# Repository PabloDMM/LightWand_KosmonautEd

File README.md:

# LightWand_KosmonautEd
This repository contains all the files related to the LightWand Kosmonaut Edition, based on the original LightWand by Michael Ross ( http://mrossphoto.com/wordpress32/ )

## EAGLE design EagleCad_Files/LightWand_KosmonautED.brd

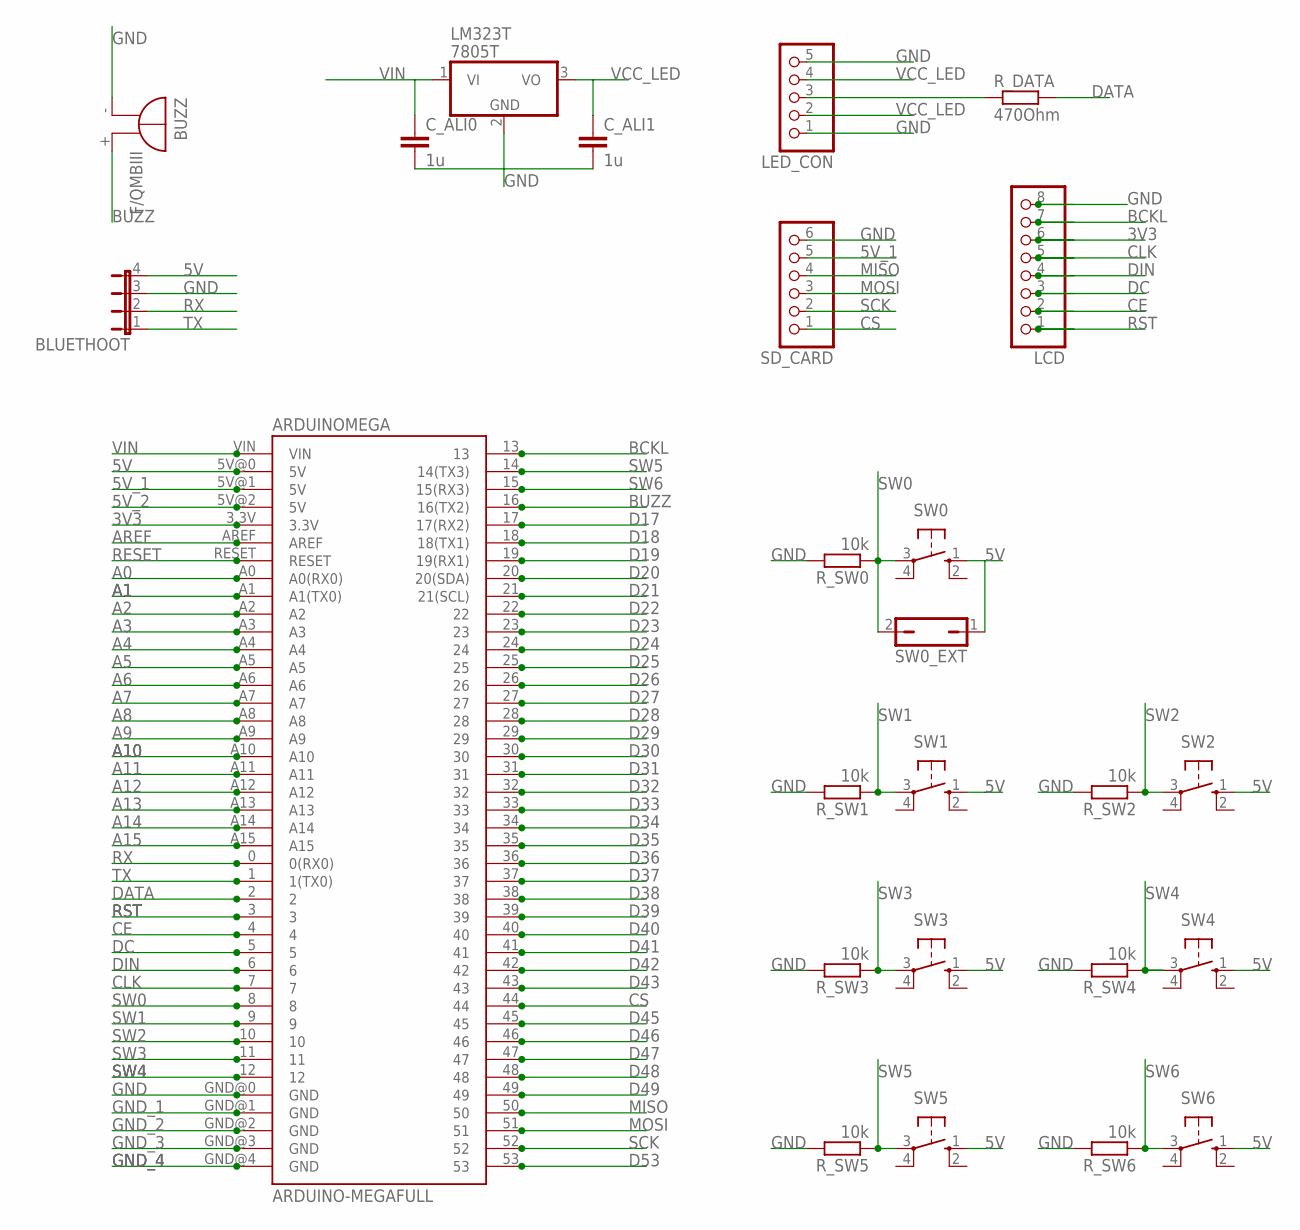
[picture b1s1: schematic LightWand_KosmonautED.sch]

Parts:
ARDUINOMEGA: ARDUINO-MEGAFULL; ARDUINO_MEGA
BLUETHOOT: JP4E; JP4
BUZZ: F/QMBIII
C_ALI0, C_ALI1: 1u; C1206
LCD: PINHD-1X8; 1X08
LED_CON: PINHD-1X5; 1X05
LM323T: 7805T; TO220H
R_DATA: 470Ohm; R1206
R_SW0, R_SW1, R_SW2, R_SW3, R_SW4, R_SW5, R_SW6: 10k; R1206
SD_CARD: PINHD-1X6; 1X06
SW0, SW1, SW2, SW3, SW4, SW5, SW6: 10-XX; B3F-10XX
SW0_EXT: JP1Q; JP1

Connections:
3V3: ARDUINOMEGA.3.3V, LCD.6
5V: ARDUINOMEGA.5V@0 (5V), BLUETHOOT.4, SW0.1 (S), SW0_EXT.1, SW1.1 (S), SW2.1 (S), SW3.1 (S), SW4.1 (S), SW5.1 (S), SW6.1 (S)
5V_1: ARDUINOMEGA.5V@1 (5V), SD_CARD.5
5V_2: ARDUINOMEGA.5V@2 (5V)
A0: ARDUINOMEGA.A0 (A0(RX0))
A1: ARDUINOMEGA.A1 (A1(TX0))
A2: ARDUINOMEGA.A2
A3: ARDUINOMEGA.A3
A4: ARDUINOMEGA.A4
A5: ARDUINOMEGA.A5
A6: ARDUINOMEGA.A6
A7: ARDUINOMEGA.A7
A8: ARDUINOMEGA.A8
A9: ARDUINOMEGA.A9
A10: ARDUINOMEGA.A10
A11: ARDUINOMEGA.A11
A12: ARDUINOMEGA.A12
A13: ARDUINOMEGA.A13
A14: ARDUINOMEGA.A14
A15: ARDUINOMEGA.A15
AREF: ARDUINOMEGA.AREF
BCKL: ARDUINOMEGA.13, LCD.7
BUZZ: ARDUINOMEGA.16 (16(TX2)), BUZZ.+ (-)
CE: ARDUINOMEGA.4, LCD.2
CLK: ARDUINOMEGA.7, LCD.5
CS: ARDUINOMEGA.44, SD_CARD.1
D17: ARDUINOMEGA.17 (17(RX2))
D18: ARDUINOMEGA.18 (18(TX1))
D19: ARDUINOMEGA.19 (19(RX1))
D20: ARDUINOMEGA.20 (20(SDA))
D21: ARDUINOMEGA.21 (21(SCL))
D22: ARDUINOMEGA.22
D23: ARDUINOMEGA.23
D24: ARDUINOMEGA.24
D25: ARDUINOMEGA.25
D26: ARDUINOMEGA.26
D27: ARDUINOMEGA.27
D28: ARDUINOMEGA.28
D29: ARDUINOMEGA.29
D30: ARDUINOMEGA.30
D31: ARDUINOMEGA.31
D32: ARDUINOMEGA.32
D33: ARDUINOMEGA.33
D34: ARDUINOMEGA.34
D35: ARDUINOMEGA.35
D36: ARDUINOMEGA.36
D37: ARDUINOMEGA.37
D38: ARDUINOMEGA.38
D39: ARDUINOMEGA.39
D40: ARDUINOMEGA.40
D41: ARDUINOMEGA.41
D42: ARDUINOMEGA.42
D43: ARDUINOMEGA.43
D45: ARDUINOMEGA.45
D46: ARDUINOMEGA.46
D47: ARDUINOMEGA.47
D48: ARDUINOMEGA.48
D49: ARDUINOMEGA.49
D53: ARDUINOMEGA.53
DATA: ARDUINOMEGA.2, R_DATA.2
DC: ARDUINOMEGA.5, LCD.3
DIN: ARDUINOMEGA.6, LCD.4
GND: ARDUINOMEGA.GND@0 (GND), BLUETHOOT.3, BUZZ.- (+), C_ALI0.2, C_ALI1.2, LCD.8, LED_CON.1, LED_CON.5, LM323T.2 (GND), R_SW0.2, R_SW1.2, R_SW2.2, R_SW3.2, R_SW4.2, R_SW5.2, R_SW6.2, SD_CARD.6
GND_1: ARDUINOMEGA.GND@1 (GND)
GND_2: ARDUINOMEGA.GND@2 (GND)
GND_3: ARDUINOMEGA.GND@3 (GND)
GND_4: ARDUINOMEGA.GND@4 (GND)
MISO: ARDUINOMEGA.50, SD_CARD.4
MOSI: ARDUINOMEGA.51, SD_CARD.3
unnamed: LED_CON.3, R_DATA.1
RESET: ARDUINOMEGA.RESET
RST: ARDUINOMEGA.3, LCD.1
RX: ARDUINOMEGA.0 (0(RX0)), BLUETHOOT.2
SCK: ARDUINOMEGA.52, SD_CARD.2
SW0: ARDUINOMEGA.8, R_SW0.1, SW0.3, SW0_EXT.2
SW1: ARDUINOMEGA.9, R_SW1.1, SW1.3
SW2: ARDUINOMEGA.10, R_SW2.1, SW2.3
SW3: ARDUINOMEGA.11, R_SW3.1, SW3.3
SW4: ARDUINOMEGA.12, R_SW4.1, SW4.3
SW5: ARDUINOMEGA.14 (14(TX3)), R_SW5.1, SW5.3
SW6: ARDUINOMEGA.15 (15(RX3)), R_SW6.1, SW6.3
TX: ARDUINOMEGA.1 (1(TX0)), BLUETHOOT.1
VCC_LED: C_ALI1.1, LED_CON.2, LED_CON.4, LM323T.3 (VO)
VIN: ARDUINOMEGA.VIN, C_ALI0.1, LM323T.1 (VI)

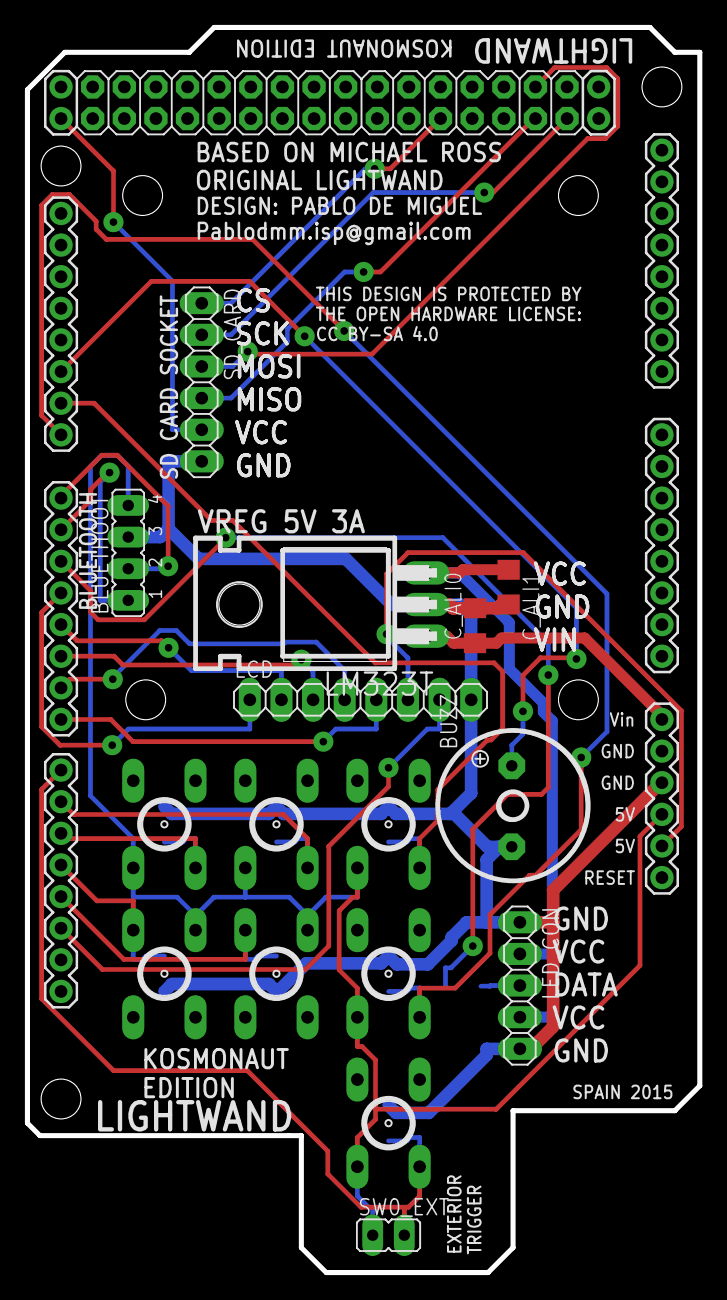
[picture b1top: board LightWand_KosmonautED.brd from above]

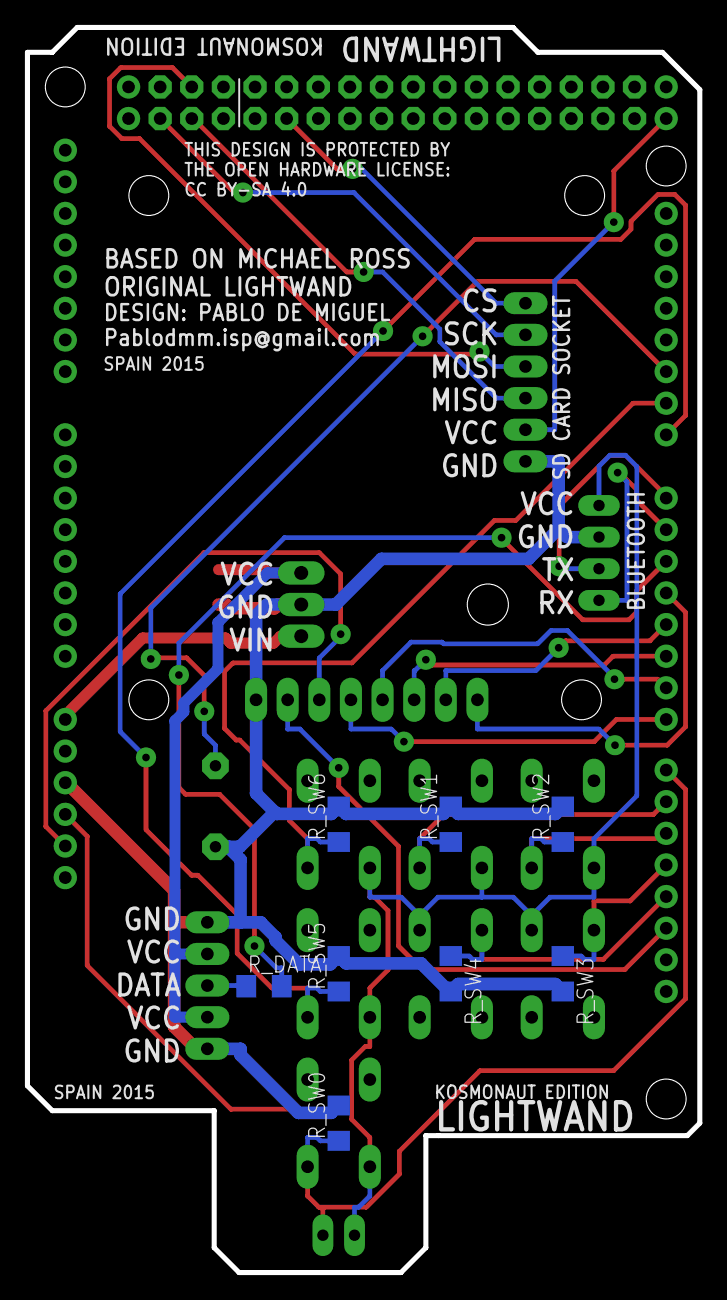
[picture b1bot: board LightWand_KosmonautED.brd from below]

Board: 2 copper layers, 54.0 x 100.0 mm, 25 parts (8 on the bottom side), 28 nets.

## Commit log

2015-05-09 Arduino Files
2015-05-09 EagleCad Files
2015-05-09 SketchUp Files
2015-05-09 Revert "Arduino Files"
    This reverts commit 28a8ee145b6e025c4e0a991c1571fa6699d76233.
2015-06-05 LightWand Kosmonaut ED Documentation
2017-12-14 Update ReadMe.md
    Minor change

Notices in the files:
EagleCad_Files/LightWand_KosmonautED.brd:
THIS DESIGN IS PROTECTED BY
THE OPEN HARDWARE LICENSE:
CC BY-SA 4.0
parts and their libraries:
SparkFun-Boards: Licensing: Creative Commons ShareAlike 4.0 International - https://creativecommons.org/licenses/by-sa/4.0
